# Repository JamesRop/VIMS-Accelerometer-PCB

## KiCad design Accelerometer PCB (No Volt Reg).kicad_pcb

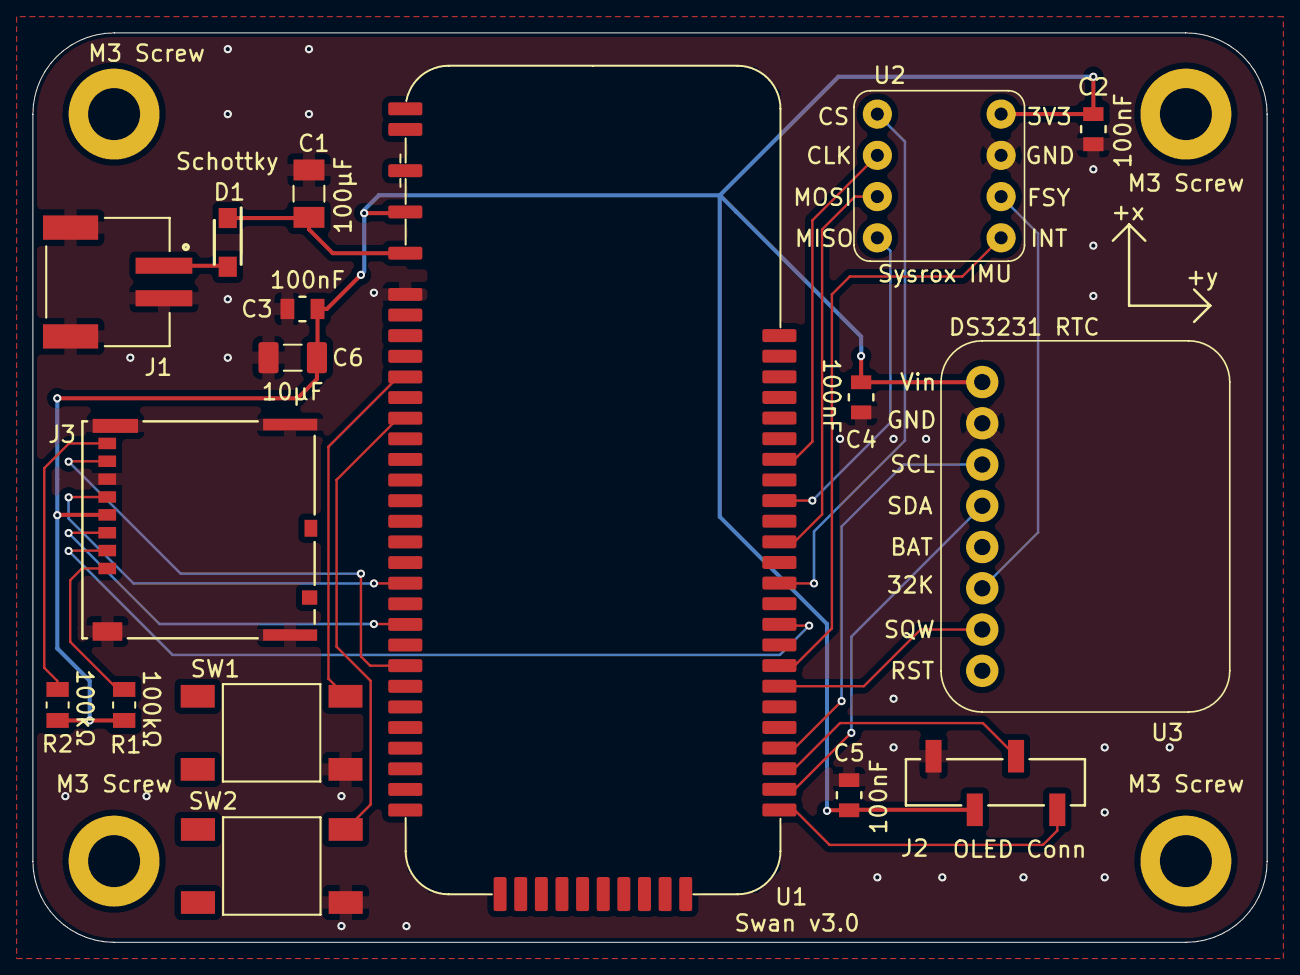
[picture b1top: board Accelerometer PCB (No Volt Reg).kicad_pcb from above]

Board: 2 copper layers, 76.0 x 56.0 mm, 21 parts (0 on the bottom side), 23 nets.

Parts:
C1: 100uF; BulkCap
C2: 100nf; Large Decoupling Capacitor
C3, C4, C5: 100nF; Large Decoupling Capacitor
C6: 10uF; 10uF External Input Cap
D1: Schottky Diode; onsemi Shottky Diode 20V 1A
J1: Power Connector; JST PH 2 pin Right Angle Connector
J2: M20-8770442; CONN4X1_NPTC041KFXC-RC_SUL
J3: MolexMicroSD; MicroSDMolex
M3 Screw, M3 Screw#2, M3 Screw#3, M3 Screw#4: MountingHole_Pad; MountingHole_3.2mm_M3_DIN965_Pad
R1, R2: 100kΩ; RESC2012X60N
SW1, SW2: SW_Push; SW_TS04-66-43-BK-260-SMT
U1: Swan v3.0; Swan v3.0 Justin's Version
U2: Sysrox Accelerometer; Sysrox SRX-IMU00-DEV
U3: Adafruit DS3231 RTC; Adafruit DS3231 Real Time Clock

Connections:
+3.3V: C2.2, C3.1, C4.1, C5.1, C6.2, J2.3 (VCC), J3.4 (VDD), R1.1, R2.2, U1.2 (3V3_REG_OUT), U2.1 (3V3), U3.1 (VCC)
/32kHz Frame Sync: U2.3 (FSY), U3.6 (32K)
/IMU Chip Select: U1.51 (D10), U2.8 (CS)
/IMU Interrupt: U1.47 (D6), U2.4 (INT)
/IMU MISO: U1.55 (D12), U2.5 (MISO)
/IMU MOSI: U1.53 (D11), U2.6 (MOSI)
/IMU Serial Clock: U1.57 (D13), U2.7 (CLK)
/MicroSD Card Detect: J3.2 (CD/DAT3), U1.49 (D9)
/MicroSD Clock Line: J3.5 (CLK), U1.18 (SCK)
/MicroSD MISO: J3.7 (DA0), U1.22 (MISO)
/MicroSD MOSI: J3.3 (CMD), U1.20 (MOSI)
/OLED Serial Clock: J2.2 (SCL), U1.42 (SCL2)
/OLED Serial Data: J2.1 (SDA), U1.40 (SDA2)
/RTC Clock Line: U1.43 (SCL), U3.3 (SCL)
/RTC Data Line: U1.41 (SDA), U3.4 (SDA)
/RTC Square Wave: U1.46 (D8), U3.7 (SQW)
/Switch 1 I/O: SW1.2, U1.8 (A1)
/Switch 2 I/O: SW2.2, U1.10 (A2)
GND: C1.2, C2.1, C3.2, C4.2, C5.2, C6.1, J1.2, J1.S1 (SHIELD), J1.S2 (SHIELD), J2.4 (GND), J3.6 (VSS), J3.11 (Pad), J3.12 (Pad), J3.13 (Pad), J3.14 (Pad), SW1.1, SW2.1, U1.4 (GND), U2.2 (GND), U3.2 (GND)
Input Power: C1.1, D1.1 (K), U1.3 (VIN)
unnamed: D1.2 (A), J1.1
unnamed: J3.8 (DAT1), R2.1
unnamed: J3.1 (DAT2), R1.2

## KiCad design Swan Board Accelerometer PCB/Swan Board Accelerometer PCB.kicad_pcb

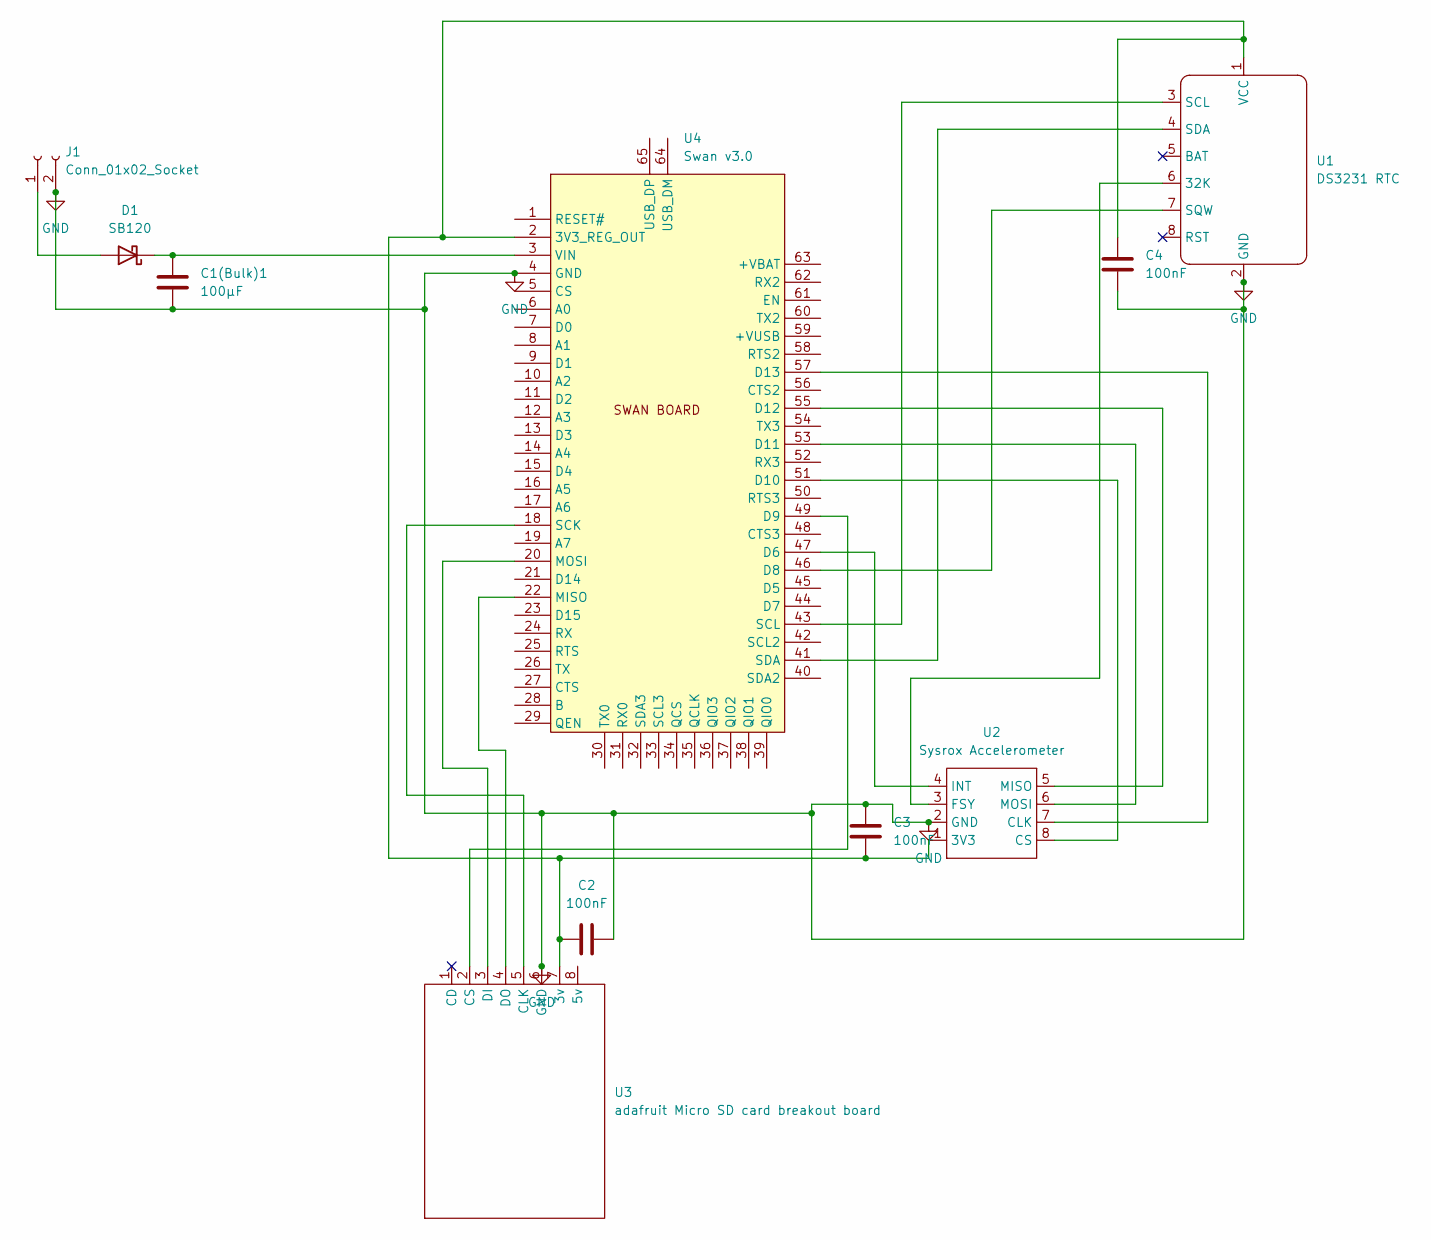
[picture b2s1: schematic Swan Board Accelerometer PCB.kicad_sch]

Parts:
C1(Bulk)1: 100µF; CAPC3216X190N
C2, C3, C4: 100nF; GRM15x
D1: SB120; SODFL3616X98N
J1: Conn_01x02_Socket; JST_PH_S2B-PH-SM4-TB_1x02-1MP_P2.00mm_Horizontal
U1: DS3231 RTC; Adafruit DS3231 Real Time Clock
U2: Sysrox Accelerometer; Sysrox SRX-IMU00-DEV
U3: adafruit Micro SD card breakout board; adafruit MicroSD card Breakout Board
U4: Swan v3.0

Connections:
GND: C1(Bulk)1.2, C2.2, C3.2, C4.1, J1.2, U1.2 (GND), U2.2 (GND), U3.6 (GND), U4.4 (GND)
unnamed: D1.2 (A), J1.1
unnamed: C1(Bulk)1.1, D1.1 (K), U4.3 (VIN)
unnamed: U1.6 (32K), U2.3 (FSY)
unnamed: U1.3 (SCL), U4.43 (SCL)
unnamed: U1.4 (SDA), U4.41 (SDA)
unnamed: U1.7 (SQW), U4.46 (D8)
unnamed: C2.1, C3.1, C4.2, U1.1 (VCC), U2.1 (3V3), U3.7 (3v), U4.2 (3V3_REG_OUT)
unnamed: U2.7 (CLK), U4.57 (D13)
unnamed: U2.8 (CS), U4.51 (D10)
unnamed: U2.4 (INT), U4.47 (D6)
unnamed: U2.5 (MISO), U4.55 (D12)
unnamed: U2.6 (MOSI), U4.53 (D11)
unnamed: U3.5 (CLK), U4.18 (SCK)
unnamed: U3.2 (CS), U4.49 (D9)
unnamed: U3.3 (DI), U4.20 (MOSI)
unnamed: U3.4 (DO), U4.22 (MISO)

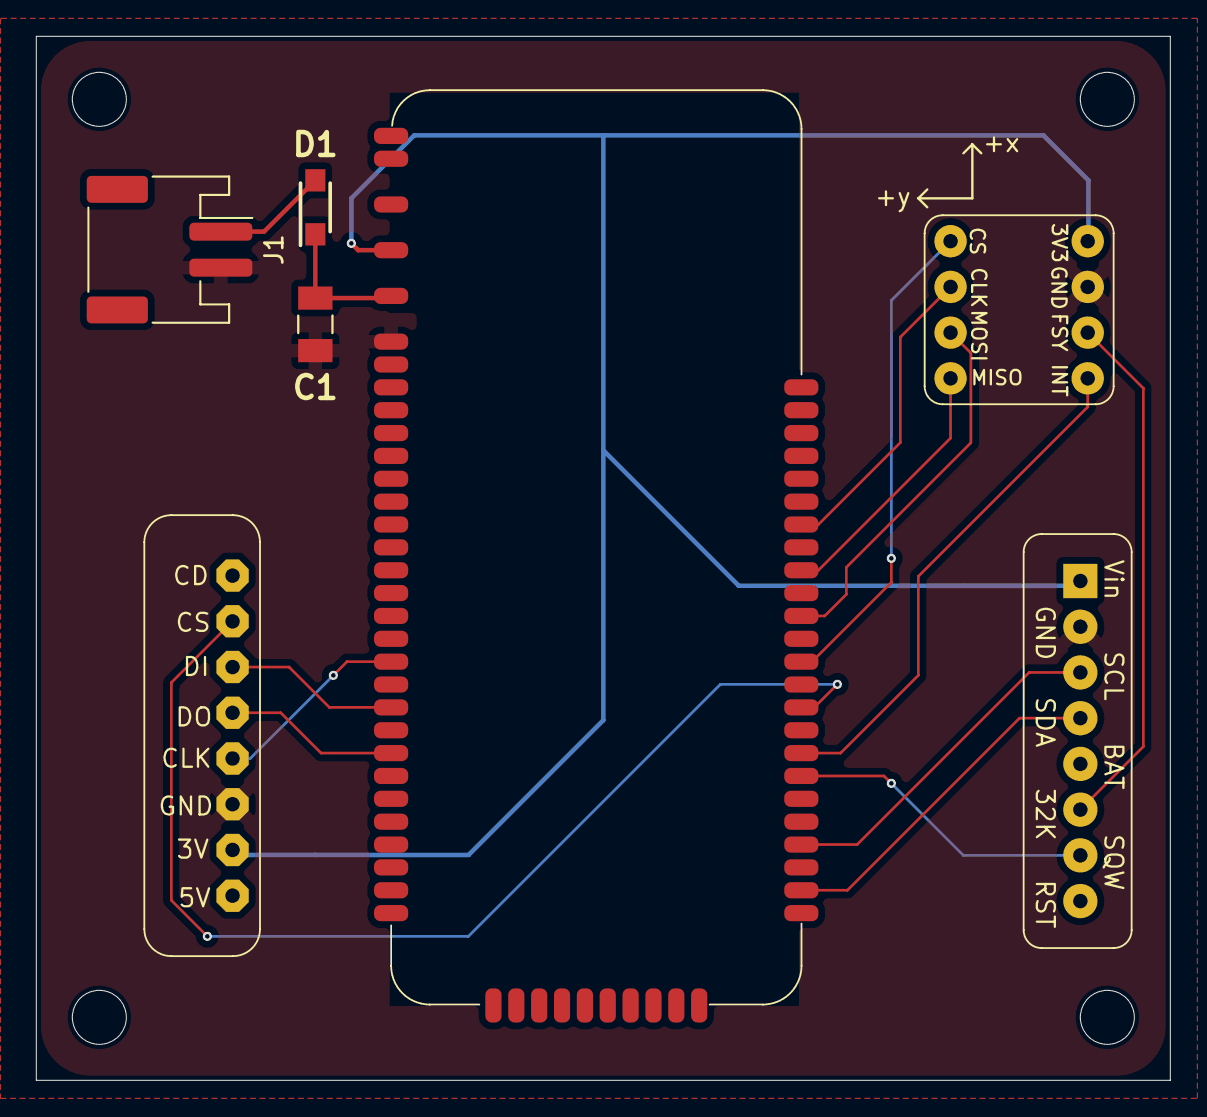
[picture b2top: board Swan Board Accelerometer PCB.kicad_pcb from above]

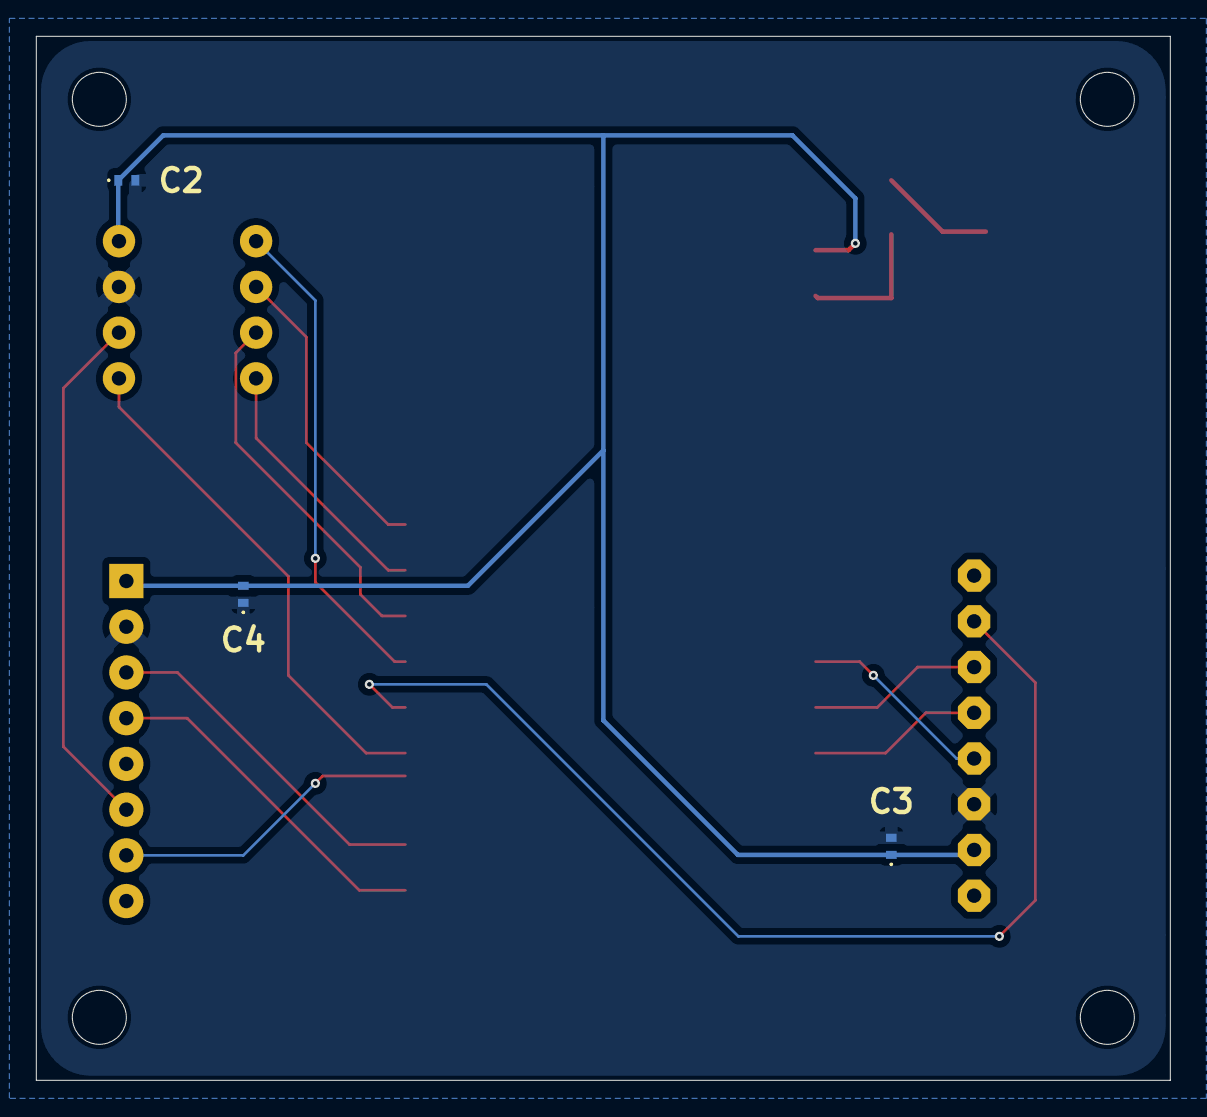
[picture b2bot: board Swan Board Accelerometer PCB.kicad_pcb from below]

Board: 2 copper layers, 63.0 x 58.0 mm, 10 parts (3 on the bottom side), 17 nets.

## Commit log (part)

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2026-06-03 updated parts list
2026-06-03 Updated footprint library
2026-06-03 Updated circuit board file
2026-06-03 Updated project file
2026-06-03 Updated schematic file
2026-06-03 Updated symbol library file
2026-06-10 Updated files for version w/o voltage regulator
2026-06-17 Added PRL File
    stores session preferences
2026-06-17 Updated Project Files
2026-06-30 Updated Screw Hole Connections and Labels
